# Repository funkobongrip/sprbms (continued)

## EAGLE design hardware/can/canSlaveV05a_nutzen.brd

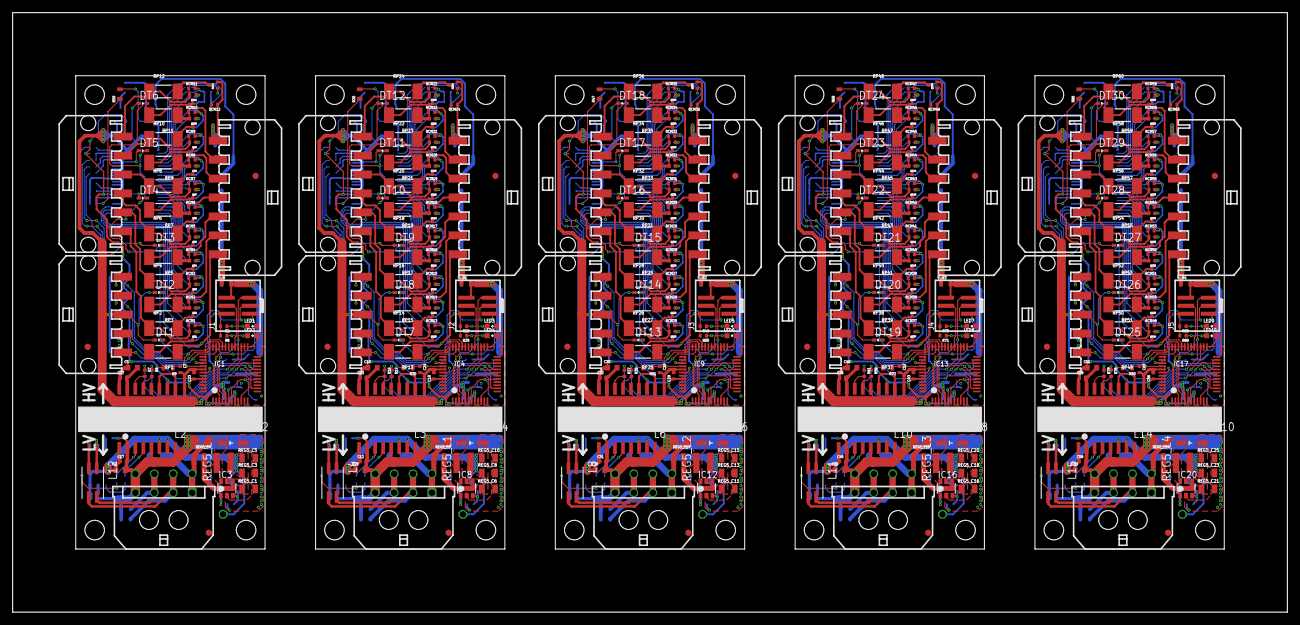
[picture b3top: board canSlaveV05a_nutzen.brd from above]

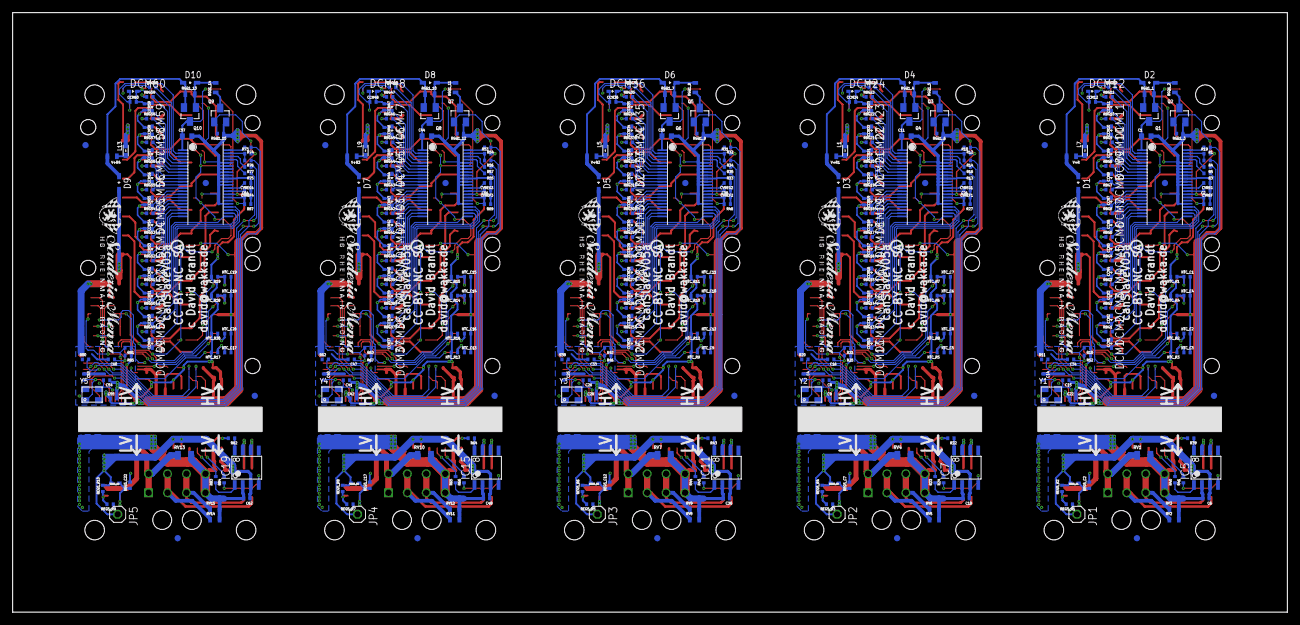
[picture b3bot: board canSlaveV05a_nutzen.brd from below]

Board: 2 copper layers, 202.0 x 95.0 mm, 830 parts (445 on the bottom side), 575 nets.

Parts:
C1, C11, C30, C44, C57: 100n,100V; C0603
C2, C3, C6, C9, C10, C12, C13, C16, C17, C19, C21, C22, C23, C24, C27, C28, C29, C31, C32, C33, C34, C36, C38, C39, C42, C43, C45, C46, C47, C49, C51, C52, C55, C56, C58, C59, C60, C62, C64, C65: 100n; C0402
C4, C8, C14, C15, C25, C26, C40, C41, C53, C54: 10p; C0402
C5, C7, C18, C20, C35, C37, C48, C50, C61, C63: 10u; C0603
CCM1, CCM2, CCM3, CCM4, CCM5, CCM6, CCM7, CCM8, CCM9, CCM10, CCM11, CCM12, CCM13, CCM14, CCM15, CCM16, CCM17, CCM18, CCM19, CCM20, CCM21, CCM22, CCM23, CCM24, CCM25, CCM26, CCM27, CCM28, CCM29, CCM30, CCM31, CCM32, CCM33, CCM34, CCM35, CCM36, CCM37, CCM38, CCM39, CCM40, CCM41, CCM42, CCM43, CCM44, CCM45, CCM46, CCM47, CCM48, CCM49, CCM50, CCM51, CCM52, CCM53, CCM54, CCM55, CCM56, CCM57, CCM58, CCM59, CCM60: 100n; C0402
CVREF, CVREF1, CVREF2, CVREF3, CVREF4: 1u; C0402
CVREG, CVREG1, CVREG2, CVREG3, CVREG4: 1u; C0402
D1, D3, D5, D7, D9: 51V; SOD323-L
D2, D4, D6, D8, D10: 12V; SOD323-L
DCM1, DCM2, DCM3, DCM4, DCM5, DCM6, DCM7, DCM8, DCM9, DCM10, DCM11, DCM12, DCM13, DCM14, DCM15, DCM16, DCM17, DCM18, DCM19, DCM20, DCM21, DCM22, DCM23, DCM24, DCM25, DCM26, DCM27, DCM28, DCM29, DCM30, DCM31, DCM32, DCM33, DCM34, DCM35, DCM36, DCM37, DCM38, DCM39, DCM40, DCM41, DCM42, DCM43, DCM44, DCM45, DCM46, DCM47, DCM48, DCM49, DCM50, DCM51, DCM52, DCM53, DCM54, DCM55, DCM56, DCM57, DCM58, DCM59, DCM60: 7.5; SOD523
DT1, DT2, DT3, DT4, DT5, DT6, DT7, DT8, DT9, DT10, DT11, DT12, DT13, DT14, DT15, DT16, DT17, DT18, DT19, DT20, DT21, DT22, DT23, DT24, DT25, DT26, DT27, DT28, DT29, DT30: 1PS79SB40; SOD523
FID1, FID2, FID3, FID4, FID5, FID6, FID7, FID8, FID9, FID10, FID11, FID12, FID13, FID14, FID15, FID16, FID17, FID18, FID19, FID20, FID21, FID22, FID23, FID24, FID25, FID26, FID27, FID28, FID29, FID30, FID31, FID32, FID33, FID34, FID35: FIDUCIAL""; FIDUCIAL_1MM
IC1, IC4, IC9, IC13, IC17: LPC11C14; LQFP48
IC2, IC6, IC10, IC14, IC18: LTC6803-4; 44SSOP
IC3, IC8, IC12, IC16, IC20: LT1616; SOT23-6
IC5, IC7, IC11, IC15, IC19: PCA82C251; SO-8
J1, J2, J3, J4, J5: PINHEAD-2X031.27SMT; 2X03_1.27MM_SMT
JP1, JP2, JP3, JP4, JP5: 1X01
L1, L5, L7, L9, L13: WE-CBF,742792664; 0603
L2, L3, L6, L10, L14: WE-PMI/74479776233A; WE-PMI_0806
L4, L8, L11, L12, L15: WE-SLM
LED1, LED3, LED5, LED7, LED9: GRN; CHIPLED_0603
LED2, LED4, LED6, LED8, LED10: RED; CHIPLED_0603
NTC_C1, NTC_C2, NTC_C3, NTC_C4, NTC_C5, NTC_C6, NTC_C7, NTC_C8, NTC_C9, NTC_C10, NTC_C11, NTC_C12, NTC_C13, NTC_C14, NTC_C15, NTC_C16, NTC_C17, NTC_C18, NTC_C19, NTC_C20: 1u; C0402
NTC_R1, NTC_R2, NTC_R3, NTC_R4, NTC_R5, NTC_R6, NTC_R7, NTC_R8, NTC_R9, NTC_R10, NTC_R11, NTC_R12, NTC_R13, NTC_R14, NTC_R15, NTC_R16, NTC_R17, NTC_R18, NTC_R19, NTC_R20: 1k; R0402
Q1, Q4, Q6, Q8, Q10: BSS84; SOT23
Q2, Q3, Q5, Q7, Q9: 2N7002; SOT23
QB1, QB2, QB3, QB4, QB5, QB6, QB7, QB8, QB9, QB10, QB11, QB12, QB13, QB14, QB15, QB16, QB17, QB18, QB19, QB20, QB21, QB22, QB23, QB24, QB25, QB26, QB27, QB28, QB29, QB30, QB31, QB32, QB33, QB34, QB35, QB36, QB37, QB38, QB39, QB40, QB41, QB42, QB43, QB44, QB45, QB46, QB47, QB48, QB49, QB50, QB51, QB52, QB53, QB54, QB55, QB56, QB57, QB58, QB59, QB60: BSS84AKT; SOT416
R1, R3, R4, R5, R6, R7, R12, R13, R14, R16, R17, R18, R23, R24, R32, R33, R34, R35, R36, R37, R40, R41, R44, R45, R54, R55, R56, R57, R58, R61, R65, R66, R74, R75, R76, R77, R78, R79, R83, R84: 100; R0402
R2, R8, R28, R29, R49, R50, R70, R71, R88, R89: 1k; R0402
R9, R30, R51, R72, R90: 3.3k; R0603
R10, R19, R31, R53, R73: 4.7k; R0402
R11, R15, R20, R21, R25, R38, R42, R46, R52, R62, R63, R67, R80, R81, R85: 10k; R0402
R22, R39, R43, R64, R82: 0; R0402
R26, R47, R59, R68, R86: 332k0.1%; R0603
R27, R48, R60, R69, R87: 20k0.1%; R0402
RBG1, RBG2, RBG3, RBG4, RBG5, RBG6, RBG7, RBG8, RBG9, RBG10, RBG11, RBG12, RBG13, RBG14, RBG15, RBG16, RBG17, RBG18, RBG19, RBG20, RBG21, RBG22, RBG23, RBG24, RBG25, RBG26, RBG27, RBG28, RBG29, RBG30, RBG31, RBG32, RBG33, RBG34, RBG35, RBG36, RBG37, RBG38, RBG39, RBG40, RBG41, RBG42, RBG43, RBG44, RBG45, RBG46, RBG47, RBG48, RBG49, RBG50, RBG51, RBG52, RBG53, RBG54, RBG55, RBG56, RBG57, RBG58, RBG59, RBG60: 3.3k; R0402
RCM1, RCM2, RCM3, RCM4, RCM5, RCM6, RCM7, RCM8, RCM9, RCM10, RCM11, RCM12, RCM13, RCM14, RCM15, RCM16, RCM17, RCM18, RCM19, RCM20, RCM21, RCM22, RCM23, RCM24, RCM25, RCM26, RCM27, RCM28, RCM29, RCM30, RCM31, RCM32, RCM33, RCM34, RCM35, RCM36, RCM37, RCM38, RCM39, RCM40, RCM41, RCM42, RCM43, RCM44, RCM45, RCM46, RCM47, RCM48, RCM49, RCM50, RCM51, RCM52, RCM53, RCM54, RCM55, RCM56, RCM57, RCM58, RCM59, RCM60: 100; R0402
REG5_C1, REG5_C4, REG5_C6, REG5_C9, REG5_C11, REG5_C14, REG5_C16, REG5_C19, REG5_C21, REG5_C24: 1u,25V,X7R; C0805
REG5_C2, REG5_C7, REG5_C12, REG5_C17, REG5_C22: 100n,>=25V,>=X5R; C0402
REG5_C3, REG5_C5, REG5_C8, REG5_C10, REG5_C13, REG5_C15, REG5_C18, REG5_C20, REG5_C23, REG5_C25: 10u,10V,X7R; C0805
REG5_D1, REG5_D3, REG5_D5, REG5_D7, REG5_D9: 1PS79SB40; SOD523
REG5_D2, REG5_D4, REG5_D6, REG5_D8, REG5_D10: PMEG6010CEH; SOD123
REG5_L, REG5_L1, REG5_L2, REG5_L3, REG5_L4: 744025100; WE-TPC_2828
REG5_R1, REG5_R3, REG5_R5, REG5_R7, REG5_R9: 10k; R0402
REG5_R2, REG5_R4, REG5_R6, REG5_R8, REG5_R10: 30.1k; R0402
RGQ1_1, RGQ1_4, RGQ1_7, RGQ1_10, RGQ1_13: 1M,50V; R0603
RGQ1_2, RGQ1_5, RGQ1_8, RGQ1_11, RGQ1_14: 100k,50V; R0603
RGQ1_3, RGQ1_6, RGQ1_9, RGQ1_12, RGQ1_15: 1M; R0402
RP1, RP2, RP3, RP4, RP5, RP6, RP7, RP8, RP9, RP10, RP11, RP12, RP13, RP14, RP15, RP16, RP17, RP18, RP19, RP20, RP21, RP22, RP23, RP24, RP25, RP26, RP27, RP28, RP29, RP30, RP31, RP32, RP33, RP34, RP35, RP36, RP37, RP38, RP39, RP40, RP41, RP42, RP43, RP44, RP45, RP46, RP47, RP48, RP49, RP50, RP51, RP52, RP53, RP54, RP55, RP56, RP57, RP58, RP59, RP60: 22; MINI_MELF-0207R
RV1, RV4, RV7, RV10, RV13: 24V; R0805
RV2, RV3, RV5, RV6, RV8, RV9, RV11, RV12, RV14, RV15: 24V; R0603
U$1, U$2, U$5, U$7, U$9: ADUM5201; SO16WB
U$3, U$4, U$6, U$8, U$10: SMLOGOS_BSILK
V+R, V+R1, V+R2, V+R3, V+R4: 100; R0603
V-R, V-R1, V-R2, V-R3, V-R4: 100; R0603
X1, X2, X9, X13, X17: 43650-0509
X3, X4, X10, X14, X18: 43650-0709
X5, X6, X11, X15, X19: 43650-0609
X7, X8, X12, X16, X20: 43045-0800
Y1, Y2, Y3, Y4, Y5: 12Mhz; MT

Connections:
!RESET: C34.1, IC1.3, J1.1, R52.2
!RESET1: C16.1, IC4.3, J2.1, R25.2
!RESET2: C33.1, IC9.3, J3.1, R46.2
!RESET3: C47.1, IC13.3, J4.1, R67.2
!RESET4: C60.1, IC17.3, J5.1, R85.2
+3V1: C9.1, C10.1, C13.1, C18.1, IC4.8, IC4.44, IC6.30, J2.2, NTC_R5.2, NTC_R6.2, NTC_R7.2, NTC_R8.2, Q3.1, R10.2, R21.1, R25.1, R28.2, R29.2, R30.2, RGQ1_6.2, U$1.P$10, U$1.P$16
+3V2: C28.1, C29.1, C32.1, C35.1, IC9.8, IC9.44, IC10.30, J3.2, NTC_R9.2, NTC_R10.2, NTC_R11.2, NTC_R12.2, Q5.1, R31.2, R42.1, R46.1, R49.2, R50.2, R51.2, RGQ1_9.2, U$5.P$10, U$5.P$16
+3V3: C5.1, C22.1, C23.1, C27.1, IC1.8, IC1.44, IC2.30, J1.2, NTC_R1.2, NTC_R2.2, NTC_R3.2, NTC_R4.2, Q2.1, R2.2, R8.2, R9.2, R15.1, R19.2, R52.1, RGQ1_3.2, U$2.P$10, U$2.P$16
+3V4: C42.1, C43.1, C46.1, C48.1, IC13.8, IC13.44, IC14.30, J4.2, NTC_R13.2, NTC_R14.2, NTC_R15.2, NTC_R16.2, Q7.1, R53.2, R63.1, R67.1, R70.2, R71.2, R72.2, RGQ1_12.2, U$7.P$10, U$7.P$16
+3V5: C55.1, C56.1, C59.1, C61.1, IC17.8, IC17.44, IC18.30, J5.2, NTC_R17.2, NTC_R18.2, NTC_R19.2, NTC_R20.2, Q9.1, R73.2, R81.1, R85.1, R88.2, R89.2, R90.2, RGQ1_15.2, U$9.P$10, U$9.P$16
BAL1: IC2.25, RBG1.2
BAL2: IC2.23, RBG2.2
BAL3: IC2.21, RBG3.2
BAL4: IC2.19, RBG4.2
BAL5: IC2.17, RBG5.2
BAL6: IC2.15, RBG6.2
BAL7: IC2.13, RBG7.2
BAL8: IC2.11, RBG8.2
BAL9: IC2.9, RBG9.2
BAL10: IC2.7, RBG10.2
BAL11: IC2.5, RBG11.2
BAL12: IC2.3, RBG12.2
BAL13: IC6.25, RBG13.2
BAL14: IC6.23, RBG14.2
BAL15: IC6.21, RBG15.2
BAL16: IC6.19, RBG16.2
BAL17: IC6.17, RBG17.2
BAL18: IC6.15, RBG18.2
BAL19: IC6.13, RBG19.2
BAL20: IC6.11, RBG20.2
BAL21: IC6.9, RBG21.2
BAL22: IC6.7, RBG22.2
BAL23: IC6.5, RBG23.2
BAL24: IC6.3, RBG24.2
BAL25: IC10.25, RBG25.2
BAL26: IC10.23, RBG26.2
BAL27: IC10.21, RBG27.2
BAL28: IC10.19, RBG28.2
BAL29: IC10.17, RBG29.2
BAL30: IC10.15, RBG30.2
BAL31: IC10.13, RBG31.2
BAL32: IC10.11, RBG32.2
BAL33: IC10.9, RBG33.2
BAL34: IC10.7, RBG34.2
BAL35: IC10.5, RBG35.2
BAL36: IC10.3, RBG36.2
BAL37: IC14.25, RBG37.2
BAL38: IC14.23, RBG38.2
BAL39: IC14.21, RBG39.2
BAL40: IC14.19, RBG40.2
BAL41: IC14.17, RBG41.2
BAL42: IC14.15, RBG42.2
BAL43: IC14.13, RBG43.2
BAL44: IC14.11, RBG44.2
BAL45: IC14.9, RBG45.2
BAL46: IC14.7, RBG46.2
BAL47: IC14.5, RBG47.2
BAL48: IC14.3, RBG48.2
BAL49: IC18.25, RBG49.2
BAL50: IC18.23, RBG50.2
BAL51: IC18.21, RBG51.2
BAL52: IC18.19, RBG52.2
BAL53: IC18.17, RBG53.2
BAL54: IC18.15, RBG54.2
BAL55: IC18.13, RBG55.2
BAL56: IC18.11, RBG56.2
BAL57: IC18.9, RBG57.2
BAL58: IC18.7, RBG58.2
BAL59: IC18.5, RBG59.2
BAL60: IC18.3, RBG60.2
BOOST1: IC3.1, REG5_C2.1, REG5_D1.C
BOOST2: IC8.1, REG5_C7.1, REG5_D3.C
BOOST3: IC12.1, REG5_C12.1, REG5_D5.C
BOOST4: IC16.1, REG5_C17.1, REG5_D7.C
BOOST5: IC20.1, REG5_C22.1, REG5_D9.C
C0: CCM1.2, D1.A, DCM1.A, IC2.26, RP1.1, V-R.1, X3.7
C1: QB1.2, RCM1.1, RP2.1, X6.1
C1M: CCM1.1, CCM2.2, DCM1.C, DCM2.A, IC2.24, RCM1.2
C1M1: CCM13.1, CCM14.2, DCM13.C, DCM14.A, IC6.24, RCM13.2
C1M2: CCM25.1, CCM26.2, DCM25.C, DCM26.A, IC10.24, RCM25.2
C1M3: CCM37.1, CCM38.2, DCM37.C, DCM38.A, IC14.24, RCM37.2
C1M4: CCM49.1, CCM50.2, DCM49.C, DCM50.A, IC18.24, RCM49.2
C2: QB2.2, RCM2.1, RP3.1, X3.6
C2M: CCM2.1, CCM3.2, DCM2.C, DCM3.A, IC2.22, RCM2.2
C2M1: CCM14.1, CCM15.2, DCM14.C, DCM15.A, IC6.22, RCM14.2
C2M2: CCM26.1, CCM27.2, DCM26.C, DCM27.A, IC10.22, RCM26.2
C2M3: CCM38.1, CCM39.2, DCM38.C, DCM39.A, IC14.22, RCM38.2
C2M4: CCM50.1, CCM51.2, DCM50.C, DCM51.A, IC18.22, RCM50.2
C3: QB3.2, RCM3.1, RP4.1, X6.2
C3M: CCM3.1, CCM4.2, DCM3.C, DCM4.A, IC2.20, RCM3.2
C3M1: CCM15.1, CCM16.2, DCM15.C, DCM16.A, IC6.20, RCM15.2
C3M2: CCM27.1, CCM28.2, DCM27.C, DCM28.A, IC10.20, RCM27.2
C3M3: CCM39.1, CCM40.2, DCM39.C, DCM40.A, IC14.20, RCM39.2
C3M4: CCM51.1, CCM52.2, DCM51.C, DCM52.A, IC18.20, RCM51.2
C4: QB4.2, RCM4.1, RP5.1, X3.5
C4M: CCM4.1, CCM5.2, DCM4.C, DCM5.A, IC2.18, RCM4.2
C4M1: CCM16.1, CCM17.2, DCM16.C, DCM17.A, IC6.18, RCM16.2
C4M2: CCM28.1, CCM29.2, DCM28.C, DCM29.A, IC10.18, RCM28.2
C4M3: CCM40.1, CCM41.2, DCM40.C, DCM41.A, IC14.18, RCM40.2
C4M4: CCM52.1, CCM53.2, DCM52.C, DCM53.A, IC18.18, RCM52.2
C5: QB5.2, RCM5.1, RP6.1, X6.3
C5M: CCM5.1, CCM6.2, DCM5.C, DCM6.A, IC2.16, RCM5.2
C5M1: CCM17.1, CCM18.2, DCM17.C, DCM18.A, IC6.16, RCM17.2
C5M2: CCM29.1, CCM30.2, DCM29.C, DCM30.A, IC10.16, RCM29.2
C5M3: CCM41.1, CCM42.2, DCM41.C, DCM42.A, IC14.16, RCM41.2
C5M4: CCM53.1, CCM54.2, DCM53.C, DCM54.A, IC18.16, RCM53.2
C6: QB6.2, RCM6.1, RP7.1, X3.4
C6M: CCM6.1, CCM7.2, DCM6.C, DCM7.A, IC2.14, RCM6.2
C6M1: CCM18.1, CCM19.2, DCM18.C, DCM19.A, IC6.14, RCM18.2
C6M2: CCM30.1, CCM31.2, DCM30.C, DCM31.A, IC10.14, RCM30.2
C6M3: CCM42.1, CCM43.2, DCM42.C, DCM43.A, IC14.14, RCM42.2
C6M4: CCM54.1, CCM55.2, DCM54.C, DCM55.A, IC18.14, RCM54.2
C7: QB7.2, RCM7.1, RP8.1, X6.4
C7M: CCM7.1, CCM8.2, DCM7.C, DCM8.A, IC2.12, RCM7.2
C7M1: CCM19.1, CCM20.2, DCM19.C, DCM20.A, IC6.12, RCM19.2
C7M2: CCM31.1, CCM32.2, DCM31.C, DCM32.A, IC10.12, RCM31.2
C7M3: CCM43.1, CCM44.2, DCM43.C, DCM44.A, IC14.12, RCM43.2
C7M4: CCM55.1, CCM56.2, DCM55.C, DCM56.A, IC18.12, RCM55.2
C8: QB8.2, RCM8.1, RP9.1, X3.3
C8M: CCM8.1, CCM9.2, DCM8.C, DCM9.A, IC2.10, RCM8.2
C8M1: CCM20.1, CCM21.2, DCM20.C, DCM21.A, IC6.10, RCM20.2
C8M2: CCM32.1, CCM33.2, DCM32.C, DCM33.A, IC10.10, RCM32.2
C8M3: CCM44.1, CCM45.2, DCM44.C, DCM45.A, IC14.10, RCM44.2
C8M4: CCM56.1, CCM57.2, DCM56.C, DCM57.A, IC18.10, RCM56.2
C9: QB9.2, RCM9.1, RP10.1, X6.5
C9M: CCM9.1, CCM10.2, DCM9.C, DCM10.A, IC2.8, RCM9.2
C9M1: CCM21.1, CCM22.2, DCM21.C, DCM22.A, IC6.8, RCM21.2
C9M2: CCM33.1, CCM34.2, DCM33.C, DCM34.A, IC10.8, RCM33.2
C9M3: CCM45.1, CCM46.2, DCM45.C, DCM46.A, IC14.8, RCM45.2
C9M4: CCM57.1, CCM58.2, DCM57.C, DCM58.A, IC18.8, RCM57.2
C10: QB10.2, RCM10.1, RP11.1, X3.2
C10M: CCM10.1, CCM11.2, DCM10.C, DCM11.A, IC2.6, RCM10.2
C10M1: CCM22.1, CCM23.2, DCM22.C, DCM23.A, IC6.6, RCM22.2
C10M2: CCM34.1, CCM35.2, DCM34.C, DCM35.A, IC10.6, RCM34.2
C10M3: CCM46.1, CCM47.2, DCM46.C, DCM47.A, IC14.6, RCM46.2
C10M4: CCM58.1, CCM59.2, DCM58.C, DCM59.A, IC18.6, RCM58.2
C11: QB11.2, RCM11.1, RP12.1, X6.6
C11M: CCM11.1, CCM12.2, DCM11.C, DCM12.A, IC2.4, RCM11.2
C11M1: CCM23.1, CCM24.2, DCM23.C, DCM24.A, IC6.4, RCM23.2
C11M2: CCM35.1, CCM36.2, DCM35.C, DCM36.A, IC10.4, RCM35.2
C11M3: CCM47.1, CCM48.2, DCM47.C, DCM48.A, IC14.4, RCM47.2
C11M4: CCM59.1, CCM60.2, DCM59.C, DCM60.A, IC18.4, RCM59.2
C12: L7.1, QB12.2, RCM12.1, X3.1
C12M: CCM12.1, DCM12.C, IC2.2, RCM12.2
C12M1: CCM24.1, DCM24.C, IC6.2, RCM24.2
C12M2: CCM36.1, DCM36.C, IC10.2, RCM36.2
C12M3: CCM48.1, DCM48.C, IC14.2, RCM48.2
C12M4: CCM60.1, DCM60.C, IC18.2, RCM60.2
C13: CCM13.2, D3.A, DCM13.A, IC6.26, RP13.1, V-R1.1, X4.7
C14: QB20.2, RCM20.1, RP21.1, X4.3
C15: QB14.2, RCM14.1, RP15.1, X4.6
C16: QB13.2, RCM13.1, RP14.1, X5.1
C17: QB15.2, RCM15.1, RP16.1, X5.2
C18: QB16.2, RCM16.1, RP17.1, X4.5
C19: QB17.2, RCM17.1, RP18.1, X5.3
C20: QB18.2, RCM18.1, RP19.1, X4.4
C21: QB19.2, RCM19.1, RP20.1, X5.4
C22: QB21.2, RCM21.1, RP22.1, X5.5
C23: QB22.2, RCM22.1, RP23.1, X4.2
C24: QB23.2, RCM23.1, RP24.1, X5.6
C25: L1.1, QB24.2, RCM24.1, X4.1
C26: CCM25.2, D5.A, DCM25.A, IC10.26, RP25.1, V-R2.1, X10.7
C27: QB32.2, RCM32.1, RP33.1, X10.3
C28: QB26.2, RCM26.1, RP27.1, X10.6
C29: QB25.2, RCM25.1, RP26.1, X11.1
C30: QB27.2, RCM27.1, RP28.1, X11.2
C31: QB28.2, RCM28.1, RP29.1, X10.5
C32: QB29.2, RCM29.1, RP30.1, X11.3
C33: QB30.2, RCM30.1, RP31.1, X10.4
C34: QB31.2, RCM31.1, RP32.1, X11.4
C35: QB33.2, RCM33.1, RP34.1, X11.5
C36: QB34.2, RCM34.1, RP35.1, X10.2
C37: QB35.2, RCM35.1, RP36.1, X11.6
C38: L5.1, QB36.2, RCM36.1, X10.1
C39: CCM37.2, D7.A, DCM37.A, IC14.26, RP37.1, V-R3.1, X14.7
C40: QB44.2, RCM44.1, RP45.1, X14.3
C41: QB38.2, RCM38.1, RP39.1, X14.6
C42: QB37.2, RCM37.1, RP38.1, X15.1
C43: QB39.2, RCM39.1, RP40.1, X15.2
C44: QB40.2, RCM40.1, RP41.1, X14.5
C45: QB41.2, RCM41.1, RP42.1, X15.3
C46: QB42.2, RCM42.1, RP43.1, X14.4
C47: QB43.2, RCM43.1, RP44.1, X15.4
C48: QB45.2, RCM45.1, RP46.1, X15.5
C49: QB46.2, RCM46.1, RP47.1, X14.2
C50: QB47.2, RCM47.1, RP48.1, X15.6
C51: L9.1, QB48.2, RCM48.1, X14.1
C52: CCM49.2, D9.A, DCM49.A, IC18.26, RP49.1, V-R4.1, X18.7
C53: QB56.2, RCM56.1, RP57.1, X18.3
C54: QB50.2, RCM50.1, RP51.1, X18.6
C55: QB49.2, RCM49.1, RP50.1, X19.1
C56: QB51.2, RCM51.1, RP52.1, X19.2
C57: QB52.2, RCM52.1, RP53.1, X18.5
C58: QB53.2, RCM53.1, RP54.1, X19.3
C59: QB54.2, RCM54.1, RP55.1, X18.4
C60: QB55.2, RCM55.1, RP56.1, X19.4
C61: QB57.2, RCM57.1, RP58.1, X19.5
C62: QB58.2, RCM58.1, RP59.1, X18.2
C63: QB59.2, RCM59.1, RP60.1, X19.6
C64: L13.1, QB60.2, RCM60.1, X18.1
CANH: L12.4, RV3.1, X7.3, X7.7
CANH1: L4.4, RV6.1, X8.3, X8.7
CANH2: L8.4, RV9.1, X12.3, X12.7
CANH3: L11.4, RV12.1, X16.3, X16.7
CANH4: L15.4, RV15.1, X20.3, X20.7
CANL: L12.3, RV2.1, X7.2, X7.6
CANL1: L4.3, RV5.1, X8.2, X8.6
CANL2: L8.3, RV8.1, X12.2, X12.6
CANL3: L11.3, RV11.1, X16.2, X16.6
CANL4: L15.3, RV14.1, X20.2, X20.6
CANRX: R7.2, U$2.P$14
CANRX1: R18.2, U$1.P$14
CANRX2: R37.2, U$5.P$14
CANRX3: R61.2, U$7.P$14
CANRX4: R79.2, U$9.P$14
CANRX_U_L: IC1.19, R7.1
CANRX_U_L1: IC4.19, R18.1
CANRX_U_L2: IC9.19, R37.1
CANRX_U_L3: IC13.19, R61.1
CANRX_U_L4: IC17.19, R79.1
CANTX: R6.2, U$2.P$13
CANTX1: R17.2, U$1.P$13
CANTX2: R36.2, U$5.P$13
CANTX3: R58.2, U$7.P$13
CANTX4: R78.2, U$9.P$13
CANTX_U_L: IC1.20, R6.1
CANTX_U_L1: IC4.20, R17.1
CANTX_U_L2: IC9.20, R36.1
CANTX_U_L3: IC13.20, R58.1
CANTX_U_L4: IC17.20, R78.1
CAR+5V: C6.1, C7.1, C17.1, IC5.3, JP1.1, REG5_C3.1, REG5_C5.1, REG5_D1.A, REG5_L.2, REG5_R2.2, U$2.P$1, U$2.P$6, U$2.P$7
CAR+5V1: C12.1, C19.1, C20.1, IC7.3, JP2.1, REG5_C8.1, REG5_C10.1, REG5_D3.A, REG5_L1.2, REG5_R4.2, U$1.P$1, U$1.P$6, U$1.P$7
CAR+5V2: C31.1, C36.1, C37.1, IC11.3, JP3.1, REG5_C13.1, REG5_C15.1, REG5_D5.A, REG5_L2.2, REG5_R6.2, U$5.P$1, U$5.P$6, U$5.P$7
CAR+5V3: C45.1, C49.1, C50.1, IC15.3, JP4.1, REG5_C18.1, REG5_C20.1, REG5_D7.A, REG5_L3.2, REG5_R8.2, U$7.P$1, U$7.P$6, U$7.P$7
CAR+5V4: C58.1, C62.1, C63.1, IC19.3, JP5.1, REG5_C23.1, REG5_C25.1, REG5_D9.A, REG5_L4.2, REG5_R10.2, U$9.P$1, U$9.P$6, U$9.P$7
CARGND: C6.2, C7.2, C17.2, IC3.2, IC5.2, R39.2, REG5_C1.2, REG5_C3.2, REG5_C4.2, REG5_C5.2, REG5_D2.2, REG5_R1.1, RV1.2, RV2.2, RV3.2, U$2.P$2, U$2.P$5, U$2.P$8, X7.4, X7.8
CARGND1: C12.2, C19.2, C20.2, IC7.2, IC8.2, R22.2, REG5_C6.2, REG5_C8.2, REG5_C9.2, REG5_C10.2, REG5_D4.2, REG5_R3.1, RV4.2, RV5.2, RV6.2, U$1.P$2, U$1.P$5, U$1.P$8, X8.4, X8.8
CARGND2: C31.2, C36.2, C37.2, IC11.2, IC12.2, R43.2, REG5_C11.2, REG5_C13.2, REG5_C14.2, REG5_C15.2, REG5_D6.2, REG5_R5.1, RV7.2, RV8.2, RV9.2, U$5.P$2, U$5.P$5, U$5.P$8, X12.4, X12.8
CARGND3: C45.2, C49.2, C50.2, IC15.2, IC16.2, R64.2, REG5_C16.2, REG5_C18.2, REG5_C19.2, REG5_C20.2, REG5_D8.2, REG5_R7.1, RV10.2, RV11.2, RV12.2, U$7.P$2, U$7.P$5, U$7.P$8, X16.4, X16.8
CARGND4: C58.2, C62.2, C63.2, IC19.2, IC20.2, R82.2, REG5_C21.2, REG5_C23.2, REG5_C24.2, REG5_C25.2, REG5_D10.2, REG5_R9.1, RV13.2, RV14.2, RV15.2, U$9.P$2, U$9.P$5, U$9.P$8, X20.4, X20.8
CARVIN: L2.1, REG5_C4.1, RV1.1, X7.1, X7.5
CARVIN1: L3.1, REG5_C9.1, RV4.1, X8.1, X8.5
CARVIN2: L6.1, REG5_C14.1, RV7.1, X12.1, X12.5
CARVIN3: L10.1, REG5_C19.1, RV10.1, X16.1, X16.5
CARVIN4: L14.1, REG5_C24.1, RV13.1, X20.1, X20.5
CARVINFILT: IC3.4, IC3.5, L2.2, REG5_C1.1
CARVINFILT1: IC8.4, IC8.5, L3.2, REG5_C6.1
CARVINFILT2: IC12.4, IC12.5, L6.2, REG5_C11.1
CARVINFILT3: IC16.4, IC16.5, L10.2, REG5_C16.1
CARVINFILT4: IC20.4, IC20.5, L14.2, REG5_C21.1
CAR_CANRX: R41.2, U$2.P$3
CAR_CANRX1: R24.2, U$1.P$3
CAR_CANRX2: R45.2, U$5.P$3
CAR_CANRX3: R66.2, U$7.P$3
CAR_CANRX4: R84.2, U$9.P$3
CAR_CANRX_T: IC5.4, R41.1
CAR_CANRX_T1: IC7.4, R24.1
CAR_CANRX_T2: IC11.4, R45.1
CAR_CANRX_T3: IC15.4, R66.1
CAR_CANRX_T4: IC19.4, R84.1
CAR_CANTX: R40.2, U$2.P$4
CAR_CANTX1: R23.2, U$1.P$4
CAR_CANTX2: R44.2, U$5.P$4
CAR_CANTX3: R65.2, U$7.P$4
CAR_CANTX4: R83.2, U$9.P$4
CAR_CANTX_T: IC5.1, R40.1
CAR_CANTX_T1: IC7.1, R23.1
CAR_CANTX_T2: IC11.1, R44.1
CAR_CANTX_T3: IC15.1, R65.1
CAR_CANTX_T4: IC19.1, R83.1
CR1: QB1.3, RP1.2
CR2: QB2.3, RP2.2
CR3: QB3.3, RP3.2
CR4: QB4.3, RP4.2
CR5: QB5.3, RP5.2
CR6: QB6.3, RP6.2
CR7: QB7.3, RP7.2
CR8: QB8.3, RP8.2
CR9: QB9.3, RP9.2
CR10: QB10.3, RP10.2
CR11: QB11.3, RP11.2
CR12: QB12.3, RP12.2
CR13: QB13.3, RP13.2
CR14: QB14.3, RP14.2
CR15: QB15.3, RP15.2
CR16: QB16.3, RP16.2
CR17: QB17.3, RP17.2
CR18: QB18.3, RP18.2
CR19: QB19.3, RP19.2
CR20: QB20.3, RP20.2
CR21: QB21.3, RP21.2
CR22: QB22.3, RP22.2
CR23: QB23.3, RP23.2
CR24: QB24.3, RP24.2
CR25: QB25.3, RP25.2
CR26: QB26.3, RP26.2
CR27: QB27.3, RP27.2
CR28: QB28.3, RP28.2
CR29: QB29.3, RP29.2
CR30: QB30.3, RP30.2
CR31: QB31.3, RP31.2
CR32: QB32.3, RP32.2
CR33: QB33.3, RP33.2
CR34: QB34.3, RP34.2
CR35: QB35.3, RP35.2
CR36: QB36.3, RP36.2
CR37: QB37.3, RP37.2
CR38: QB38.3, RP38.2
CR39: QB39.3, RP39.2
CR40: QB40.3, RP40.2
CR41: QB41.3, RP41.2
CR42: QB42.3, RP42.2
CR43: QB43.3, RP43.2
CR44: QB44.3, RP44.2
CR45: QB45.3, RP45.2
CR46: QB46.3, RP46.2
CR47: QB47.3, RP47.2
CR48: QB48.3, RP48.2
CR49: QB49.3, RP49.2
CR50: QB50.3, RP50.2
CR51: QB51.3, RP51.2
CR52: QB52.3, RP52.2
CR53: QB53.3, RP53.2
CR54: QB54.3, RP54.2
CR55: QB55.3, RP55.2
CR56: QB56.3, RP56.2
CR57: QB57.3, RP57.2
CR58: QB58.3, RP58.2
CR59: QB59.3, RP59.2
CR60: QB60.3, RP60.2
CSB: IC2.44, R1.2
CSB1: IC6.44, R12.2
CSB2: IC10.44, R32.2
CSB3: IC14.44, R54.2
CSB4: IC18.44, R74.2
FB1: IC3.3, REG5_R1.2, REG5_R2.1
FB2: IC8.3, REG5_R3.2, REG5_R4.1
FB3: IC12.3, REG5_R5.2, REG5_R6.1
FB4: IC16.3, REG5_R7.2, REG5_R8.1
FB5: IC20.3, REG5_R9.2, REG5_R10.1
FSM: C2.1, IC2.29, R59.1, R60.2
FSM1: C21.1, IC6.29, R26.1, R27.2
FSM2: C38.1, IC10.29, R47.1, R48.2
FSM3: C51.1, IC14.29, R68.1, R69.2
FSM4: C64.1, IC18.29, R86.1, R87.2
GND: C1.2, C2.2, C3.2, C5.2, C14.1, C15.1, C22.2, C23.2, C27.2, C34.2, CVREF.1, CVREG.1, DT1.C, DT2.C, DT3.C, DT4.C, DT5.C, DT6.C, IC1.5, IC1.41, IC2.27, IC2.33, IC2.34, IC2.35, IC2.36, IC2.37, IC2.38, IC2.39, IC2.40, J1.6, NTC_C1.2, NTC_C2.2, NTC_C3.2, NTC_C4.2, Q2.2, R11.1, R60.1, RGQ1_3.1, U$2.P$9, U$2.P$11, U$2.P$15, V-R.2, X1.3, Y1.P2, Y1.P4
GND1: C4.1, C8.1, C9.2, C10.2, C11.2, C13.2, C16.2, C18.2, C21.2, C24.2, CVREF1.1, CVREG1.1, DT7.C, DT8.C, DT9.C, DT10.C, DT11.C, DT12.C, IC4.5, IC4.41, IC6.27, IC6.33, IC6.34, IC6.35, IC6.36, IC6.37, IC6.38, IC6.39, IC6.40, J2.6, NTC_C5.2, NTC_C6.2, NTC_C7.2, NTC_C8.2, Q3.2, R20.1, R27.1, RGQ1_6.1, U$1.P$9, U$1.P$11, U$1.P$15, V-R1.2, X2.3, Y2.P2, Y2.P4
GND2: C25.1, C26.1, C28.2, C29.2, C30.2, C32.2, C33.2, C35.2, C38.2, C39.2, CVREF2.1, CVREG2.1, DT13.C, DT14.C, DT15.C, DT16.C, DT17.C, DT18.C, IC9.5, IC9.41, IC10.27, IC10.33, IC10.34, IC10.35, IC10.36, IC10.37, IC10.38, IC10.39, IC10.40, J3.6, NTC_C9.2, NTC_C10.2, NTC_C11.2, NTC_C12.2, Q5.2, R38.1, R48.1, RGQ1_9.1, U$5.P$9, U$5.P$11, U$5.P$15, V-R2.2, X9.3, Y3.P2, Y3.P4
GND3: C40.1, C41.1, C42.2, C43.2, C44.2, C46.2, C47.2, C48.2, C51.2, C52.2, CVREF3.1, CVREG3.1, DT19.C, DT20.C, DT21.C, DT22.C, DT23.C, DT24.C, IC13.5, IC13.41, IC14.27, IC14.33, IC14.34, IC14.35, IC14.36, IC14.37, IC14.38, IC14.39, IC14.40, J4.6, NTC_C13.2, NTC_C14.2, NTC_C15.2, NTC_C16.2, Q7.2, R62.1, R69.1, RGQ1_12.1, U$7.P$9, U$7.P$11, U$7.P$15, V-R3.2, X13.3, Y4.P2, Y4.P4
GND4: C53.1, C54.1, C55.2, C56.2, C57.2, C59.2, C60.2, C61.2, C64.2, C65.2, CVREF4.1, CVREG4.1, DT25.C, DT26.C, DT27.C, DT28.C, DT29.C, DT30.C, IC17.5, IC17.41, IC18.27, IC18.33, IC18.34, IC18.35, IC18.36, IC18.37, IC18.38, IC18.39, IC18.40, J5.6, NTC_C17.2, NTC_C18.2, NTC_C19.2, NTC_C20.2, Q9.2, R80.1, R87.1, RGQ1_15.1, U$9.P$9, U$9.P$11, U$9.P$15, V-R4.2, X17.3, Y5.P2, Y5.P4
ISP_CAN: IC1.14, R11.2
ISP_CAN1: IC4.14, R20.2
ISP_CAN2: IC9.14, R38.2
ISP_CAN3: IC13.14, R62.2
ISP_CAN4: IC17.14, R80.2
ISP_ENTER: IC1.4, J1.5, R15.2
ISP_ENTER1: IC4.4, J2.5, R21.2
ISP_ENTER2: IC9.4, J3.5, R42.2
ISP_ENTER3: IC13.4, J4.5, R63.2
ISP_ENTER4: IC17.4, J5.5, R81.2
LED1: IC1.24, LED1.C
LED2: IC1.25, LED2.C
LED3: IC4.24, LED3.C
LED4: IC4.25, LED4.C
LED5: IC9.24, LED5.C
LED6: IC9.25, LED6.C
LED7: IC13.24, LED7.C
LED8: IC13.25, LED8.C
LED9: IC17.24, LED9.C
LED10: IC17.25, LED10.C
MISO0: IC1.27, R4.1
MISO3: IC4.27, R14.1
MISO5: IC9.27, R34.1
MISO7: IC13.27, R56.1
MISO9: IC17.27, R76.1
MOSI0: IC1.28, R5.1
MOSI3: IC4.28, R16.1
MOSI5: IC9.28, R35.1
MOSI7: IC13.28, R57.1
MOSI9: IC17.28, R77.1
unnamed: LED2.A, R8.1
unnamed: IC5.7, L12.1
unnamed: Q2.3, RGQ1_2.1
unnamed: L7.2, V+R.1
unnamed: LED1.A, R2.1
unnamed: IC5.6, L12.2
unnamed: Q3.3, RGQ1_5.1
unnamed: L1.2, V+R1.1
unnamed: LED3.A, R28.1
unnamed: LED4.A, R29.1
unnamed: IC7.7, L4.1
unnamed: IC7.6, L4.2
unnamed: Q5.3, RGQ1_8.1
unnamed: L5.2, V+R2.1
unnamed: LED5.A, R49.1
unnamed: LED6.A, R50.1
unnamed: IC11.7, L8.1
unnamed: IC11.6, L8.2
unnamed: Q7.3, RGQ1_11.1
unnamed: L9.2, V+R3.1
unnamed: LED7.A, R70.1
unnamed: LED8.A, R71.1
unnamed: IC15.7, L11.1
unnamed: IC15.6, L11.2
unnamed: Q9.3, RGQ1_14.1
unnamed: L13.2, V+R4.1
unnamed: LED9.A, R88.1
unnamed: LED10.A, R89.1
unnamed: IC19.7, L15.1
unnamed: IC19.6, L15.2
Q1G: D2.A, Q1.1, RGQ1_1.2, RGQ1_2.2
Q1G1: D4.A, Q4.1, RGQ1_4.2, RGQ1_5.2
Q1G2: D6.A, Q6.1, RGQ1_7.2, RGQ1_8.2
Q1G3: D8.A, Q8.1, RGQ1_10.2, RGQ1_11.2
Q1G4: D10.A, Q10.1, RGQ1_13.2, RGQ1_14.2
QBG1: QB1.1, RBG1.1
QBG2: QB2.1, RBG2.1
QBG3: QB3.1, RBG3.1
QBG4: QB4.1, RBG4.1
QBG5: QB5.1, RBG5.1
QBG6: QB6.1, RBG6.1
QBG7: QB7.1, RBG7.1
QBG8: QB8.1, RBG8.1
QBG9: QB9.1, RBG9.1
QBG10: QB10.1, RBG10.1
QBG11: QB11.1, RBG11.1
QBG12: QB12.1, RBG12.1
QBG13: QB13.1, RBG13.1
QBG14: QB14.1, RBG14.1
QBG15: QB15.1, RBG15.1
QBG16: QB16.1, RBG16.1
QBG17: QB17.1, RBG17.1
QBG18: QB18.1, RBG18.1
QBG19: QB19.1, RBG19.1
QBG20: QB20.1, RBG20.1
QBG21: QB21.1, RBG21.1
QBG22: QB22.1, RBG22.1
QBG23: QB23.1, RBG23.1
QBG24: QB24.1, RBG24.1
QBG25: QB25.1, RBG25.1
QBG26: QB26.1, RBG26.1
QBG27: QB27.1, RBG27.1
QBG28: QB28.1, RBG28.1
QBG29: QB29.1, RBG29.1
QBG30: QB30.1, RBG30.1
QBG31: QB31.1, RBG31.1
QBG32: QB32.1, RBG32.1
QBG33: QB33.1, RBG33.1
QBG34: QB34.1, RBG34.1
QBG35: QB35.1, RBG35.1
QBG36: QB36.1, RBG36.1
QBG37: QB37.1, RBG37.1
QBG38: QB38.1, RBG38.1
QBG39: QB39.1, RBG39.1
QBG40: QB40.1, RBG40.1
QBG41: QB41.1, RBG41.1
QBG42: QB42.1, RBG42.1
QBG43: QB43.1, RBG43.1
QBG44: QB44.1, RBG44.1
QBG45: QB45.1, RBG45.1
QBG46: QB46.1, RBG46.1
QBG47: QB47.1, RBG47.1
QBG48: QB48.1, RBG48.1
QBG49: QB49.1, RBG49.1
QBG50: QB50.1, RBG50.1
QBG51: QB51.1, RBG51.1
QBG52: QB52.1, RBG52.1
QBG53: QB53.1, RBG53.1
QBG54: QB54.1, RBG54.1
QBG55: QB55.1, RBG55.1
QBG56: QB56.1, RBG56.1
QBG57: QB57.1, RBG57.1
QBG58: QB58.1, RBG58.1
QBG59: QB59.1, RBG59.1
QBG60: QB60.1, RBG60.1
RS1: IC5.8, R39.1
RS2: IC7.8, R22.1
RS3: IC11.8, R43.1
RS4: IC15.8, R64.1
RS5: IC19.8, R82.1
SCK: IC2.41, R3.2
SCK0: IC1.22, R3.1
SCK2: IC6.41, R13.2
SCK4: IC4.22, R13.1
SCK5: IC10.41, R33.2
SCK7: IC9.22, R33.1
SCK8: IC14.41, R55.2
SCK10: IC13.22, R55.1
SCK11: IC18.41, R75.2
SCK13: IC17.22, R75.1
SDI: IC2.42, R5.2
SDI1: IC6.42, R16.2
SDI2: IC10.42, R35.2
SDI3: IC14.42, R57.2
SDI4: IC18.42, R77.2
SDO: IC2.43, R4.2, R19.1
SDO1: IC6.43, R10.1, R14.2
SDO2: IC10.43, R31.1, R34.2
SDO3: IC14.43, R53.1, R56.2
SDO4: IC18.43, R73.1, R76.2
SSEL0: IC1.10, R1.1
SSEL3: IC4.10, R12.1
SSEL5: IC9.10, R32.1
SSEL7: IC13.10, R54.1
SSEL9: IC17.10, R74.1
SW1: IC3.6, REG5_C2.2, REG5_D2.1, REG5_L.1
SW2: IC8.6, REG5_C7.2, REG5_D4.1, REG5_L1.1
SW3: IC12.6, REG5_C12.2, REG5_D6.1, REG5_L2.1
SW4: IC16.6, REG5_C17.2, REG5_D8.1, REG5_L3.1
SW5: IC20.6, REG5_C22.2, REG5_D10.1, REG5_L4.1
SWCLK: IC1.29, J1.4
SWCLK1: IC4.29, J2.4
SWCLK2: IC9.29, J3.4
SWCLK3: IC13.29, J4.4
SWCLK4: IC17.29, J5.4
SWDIO: IC1.39, J1.3
SWDIO1: IC4.39, J2.3
SWDIO2: IC9.39, J3.3
SWDIO3: IC13.39, J4.3
SWDIO4: IC17.39, J5.3
TEMP0: IC1.42, NTC_C3.1, NTC_R3.1, X1.1
TEMP1: IC1.40, NTC_C2.1, NTC_R2.1, X1.2
TEMP2: IC1.35, NTC_C4.1, NTC_R4.1, X1.4
TEMP3: IC1.34, NTC_C1.1, NTC_R1.1, X1.5
TEMP4: IC4.42, NTC_C5.1, NTC_R5.1, X2.1
TEMP5: IC4.35, NTC_C6.1, NTC_R6.1, X2.4
TEMP6: IC4.34, NTC_C7.1, NTC_R7.1, X2.5
TEMP7: IC4.40, NTC_C8.1, NTC_R8.1, X2.2
TEMP8: IC9.42, NTC_C9.1, NTC_R9.1, X9.1
TEMP9: IC9.35, NTC_C10.1, NTC_R10.1, X9.4
TEMP10: IC9.34, NTC_C11.1, NTC_R11.1, X9.5
TEMP11: IC9.40, NTC_C12.1, NTC_R12.1, X9.2
TEMP12: IC13.42, NTC_C13.1, NTC_R13.1, X13.1
TEMP13: IC13.35, NTC_C14.1, NTC_R14.1, X13.4
TEMP14: IC13.34, NTC_C15.1, NTC_R15.1, X13.5
TEMP15: IC13.40, NTC_C16.1, NTC_R16.1, X13.2
TEMP16: IC17.42, NTC_C17.1, NTC_R17.1, X17.1
TEMP17: IC17.35, NTC_C18.1, NTC_R18.1, X17.4
TEMP18: IC17.34, NTC_C19.1, NTC_R19.1, X17.5
TEMP19: IC17.40, NTC_C20.1, NTC_R20.1, X17.2
TEMPR: C3.1, DT1.A, DT2.A, DT3.A, DT4.A, DT5.A, DT6.A, IC1.33, R9.1
TEMPR1: C24.1, DT7.A, DT8.A, DT9.A, DT10.A, DT11.A, DT12.A, IC4.33, R30.1
TEMPR2: C39.1, DT13.A, DT14.A, DT15.A, DT16.A, DT17.A, DT18.A, IC9.33, R51.1
TEMPR3: C52.1, DT19.A, DT20.A, DT21.A, DT22.A, DT23.A, DT24.A, IC13.33, R72.1
TEMPR4: C65.1, DT25.A, DT26.A, DT27.A, DT28.A, DT29.A, DT30.A, IC17.33, R90.1
V+: C1.1, IC2.1, Q1.3, R59.2
V+1: C11.1, IC6.1, Q4.3, R26.2
V+2: C30.1, IC10.1, Q6.3, R47.2
V+3: C44.1, IC14.1, Q8.3, R68.2
V+4: C57.1, IC18.1, Q10.3, R86.2
V+S: D1.C, D2.C, Q1.2, RGQ1_1.1, V+R.2
V+S1: D3.C, D4.C, Q4.2, RGQ1_4.1, V+R1.2
V+S2: D5.C, D6.C, Q6.2, RGQ1_7.1, V+R2.2
V+S3: D7.C, D8.C, Q8.2, RGQ1_10.1, V+R3.2
V+S4: D9.C, D10.C, Q10.2, RGQ1_13.1, V+R4.2
VREF: CVREF.2, IC2.31
VREF1: CVREF1.2, IC6.31
VREF2: CVREF2.2, IC10.31
VREF3: CVREF3.2, IC14.31
VREF4: CVREF4.2, IC18.31
VREG: CVREG.2, IC2.32
VREG1: CVREG1.2, IC6.32
VREG2: CVREG2.2, IC10.32
VREG3: CVREG3.2, IC14.32
VREG4: CVREG4.2, IC18.32
XTALIN: C15.2, IC1.6, Y1.P3
XTALIN1: C8.2, IC4.6, Y2.P3
XTALIN2: C26.2, IC9.6, Y3.P3
XTALIN3: C41.2, IC13.6, Y4.P3
XTALIN4: C54.2, IC17.6, Y5.P3
XTALOUT: C14.2, IC1.7, Y1.P1
XTALOUT1: C4.2, IC4.7, Y2.P1
XTALOUT2: C25.2, IC9.7, Y3.P1
XTALOUT3: C40.2, IC13.7, Y4.P1
XTALOUT4: C53.2, IC17.7, Y5.P1
